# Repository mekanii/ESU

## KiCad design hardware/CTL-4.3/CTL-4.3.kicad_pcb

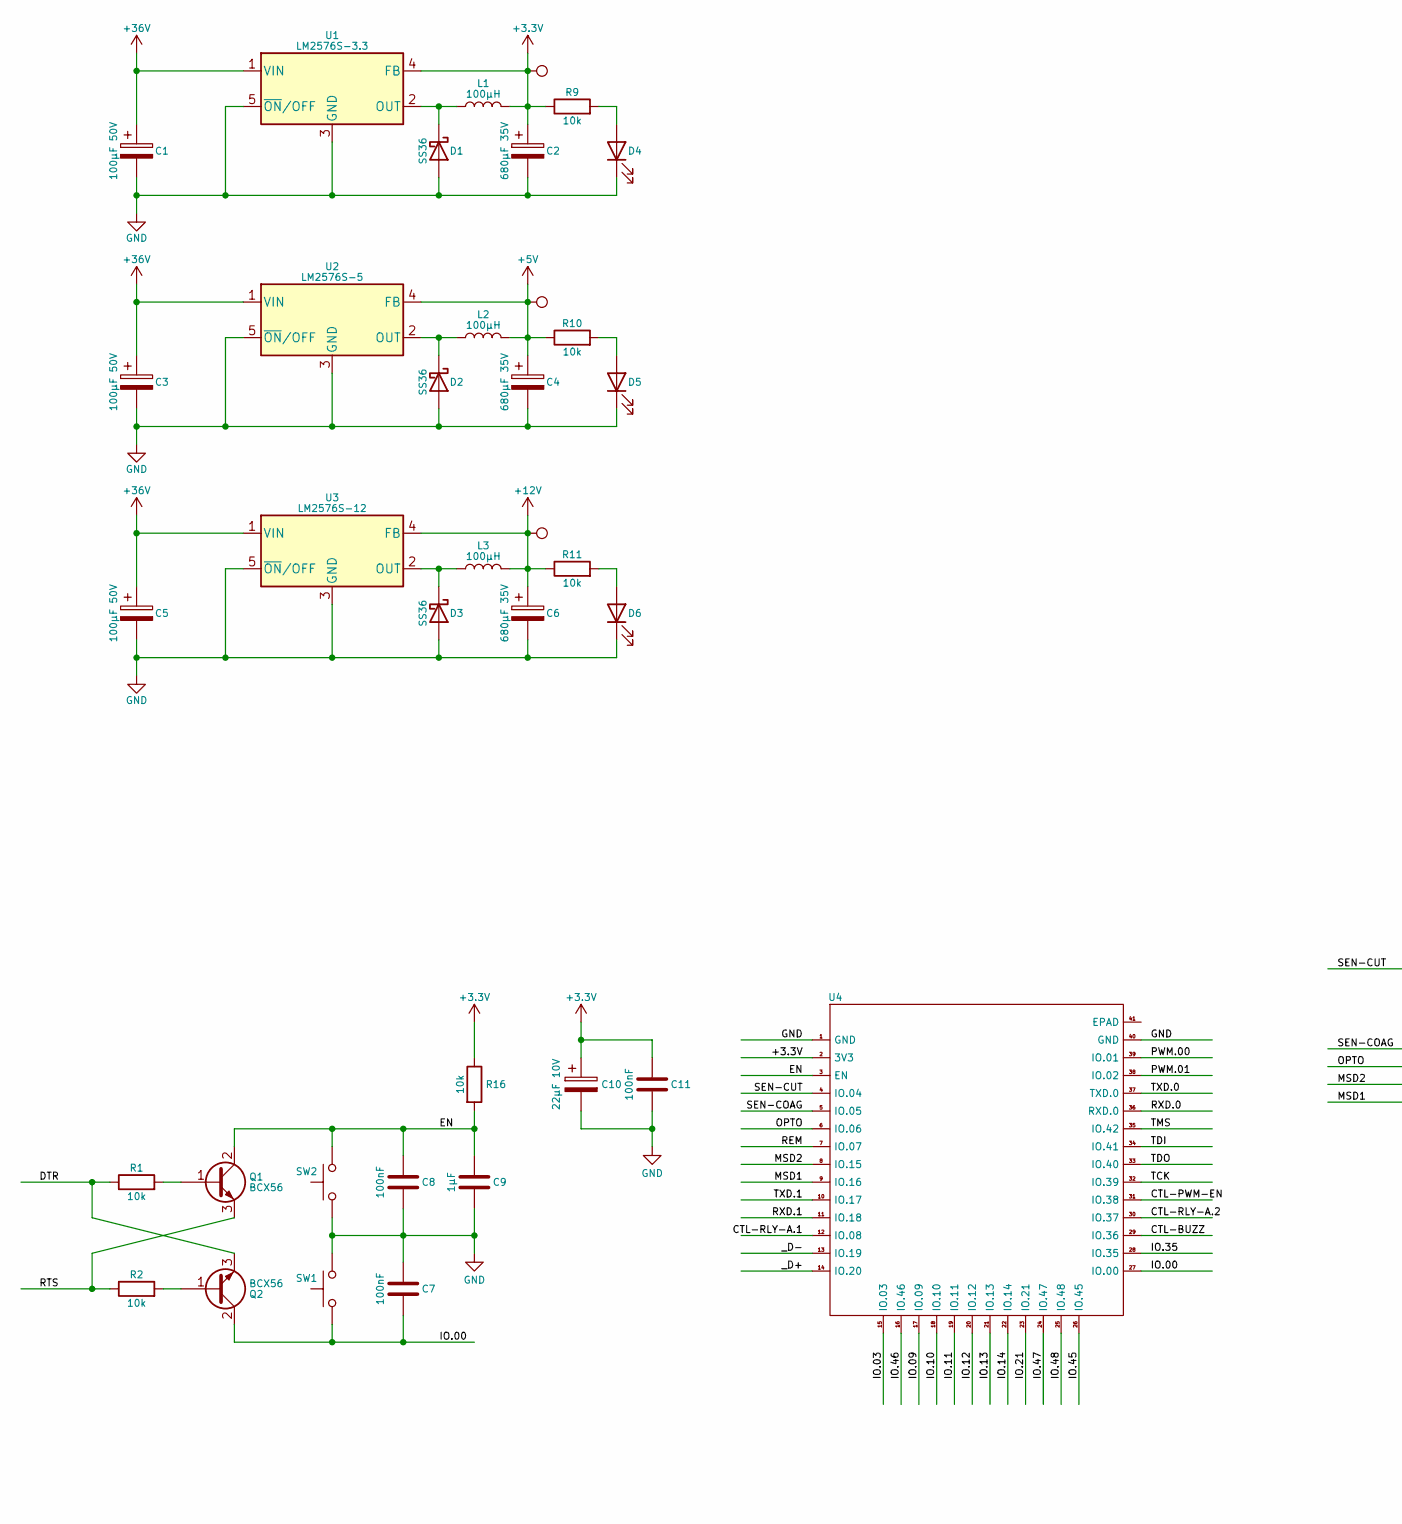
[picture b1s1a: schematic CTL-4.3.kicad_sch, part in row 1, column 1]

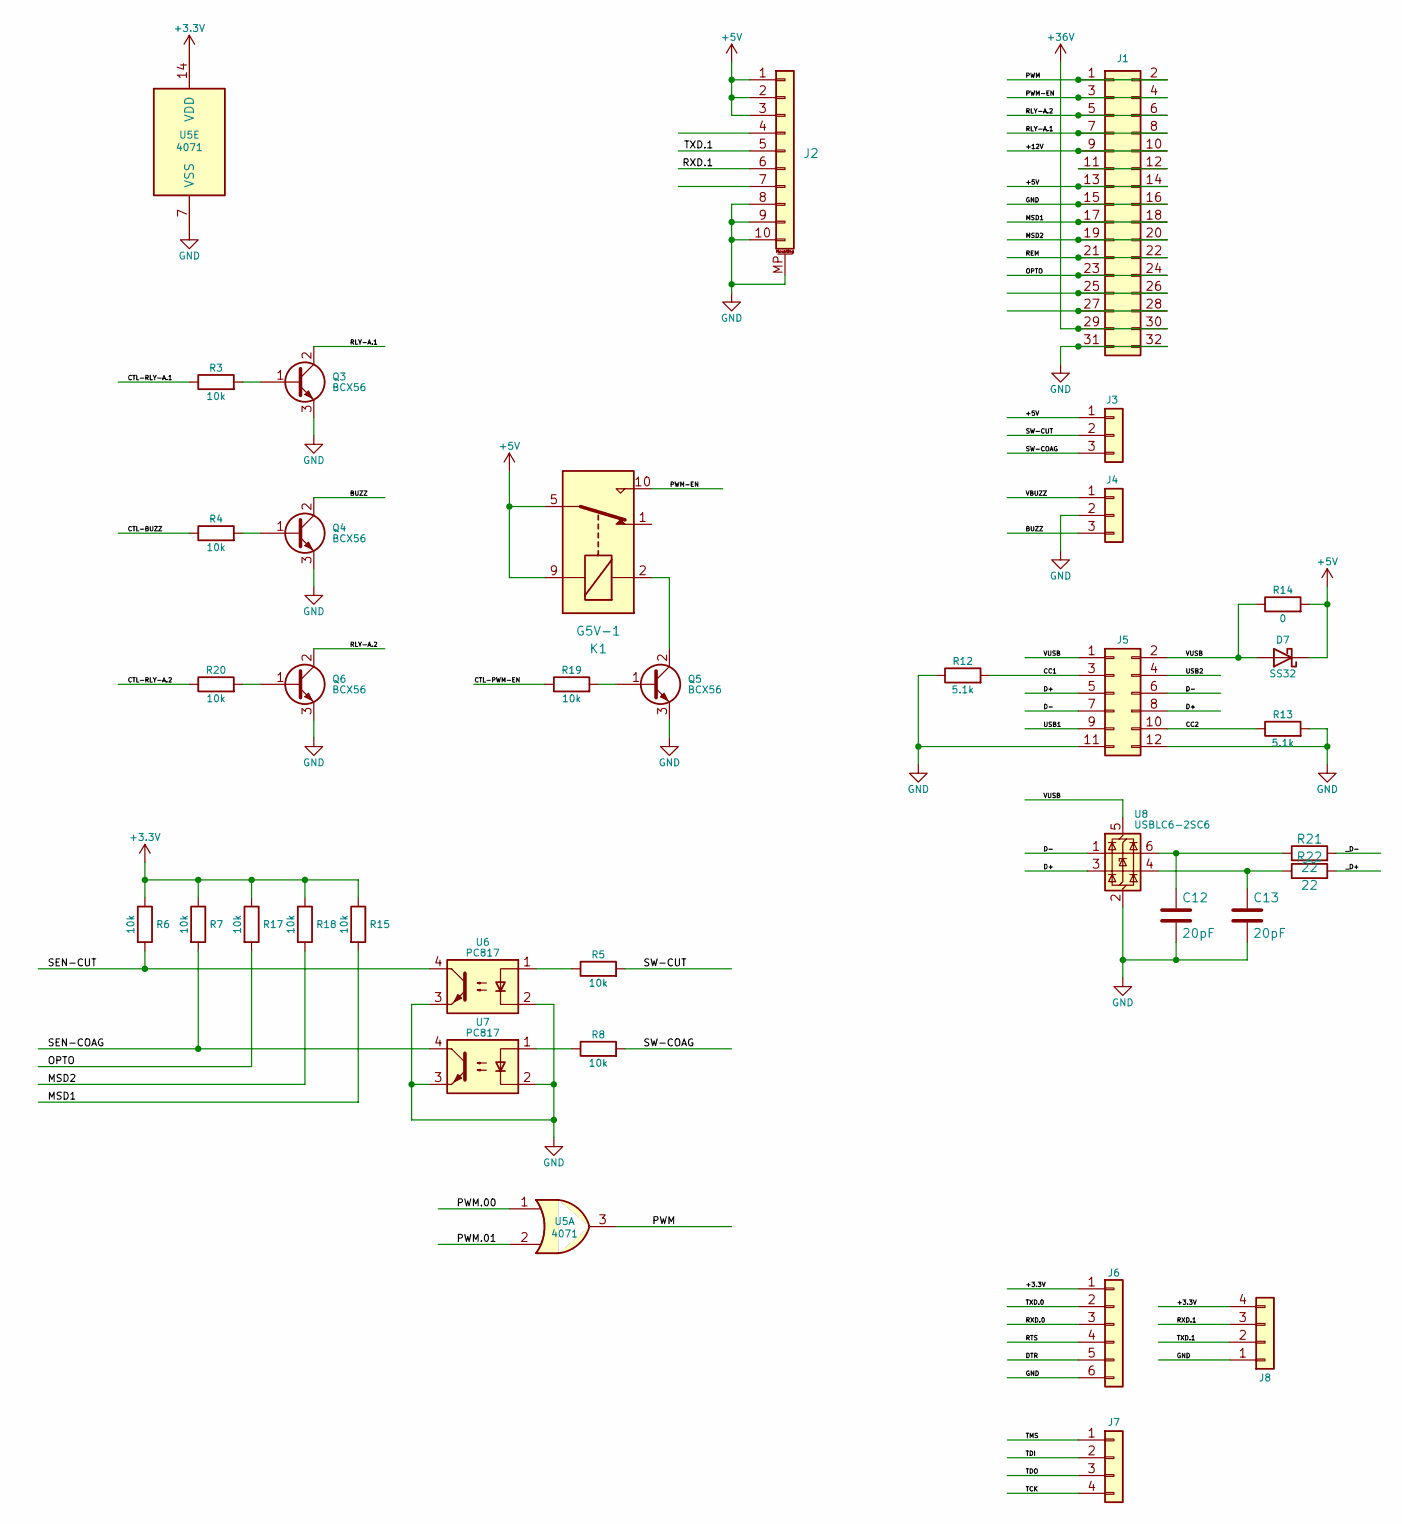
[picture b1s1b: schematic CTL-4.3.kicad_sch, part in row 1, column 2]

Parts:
C1, C3, C5: 100µF 50V; CP_Elec_10x10
C2, C4, C6: 680µF 35V; CP_Elec_10x10
C7, C8, C11: 100nF; C_0805_2012Metric_Pad1.18x1.45mm_HandSolder
C9: 1µF; C_0805_2012Metric_Pad1.18x1.45mm_HandSolder
C10: 22µF 10V; CP_EIA-3216-18_Kemet-A_Pad1.58x1.35mm_HandSolder
C12, C13: 20pF; C_0805_2012Metric_Pad1.18x1.45mm_HandSolder
D1, D2, D3: SS36; D_SMA
D4, D5, D6: LED; LED_0805_2012Metric_Pad1.15x1.40mm_HandSolder
D7: SS32; D_SMA
J1: Conn_02x16_Top_Bottom; PinHeader_2x16_P2.54mm_Horizontal_NoPins
J2: TE_1-84952-0_1x10-1MP_P1.0mm_Horizontal
J3, J4: Conn_01x03; JST_XH_B3B-XH-A_1x03_P2.50mm_Vertical
J5: Conn_02x06_Odd_Even; PinHeader_2x06_P2.54mm_Vertical
J6: Conn_01x04; PinHeader_1x06_P2.54mm_Vertical
J7, J8: Conn_01x04; PinHeader_1x04_P2.54mm_Vertical
K1: G5V-1; Relay_SPDT_Omron_G5V-1
L1, L2, L3: 100µH; L_12x12mm_H8mm
Q1, Q2, Q3, Q4, Q5, Q6: BCX56; SOT-89-3
R1, R2, R3, R4, R5, R6, R7, R8, R9, R10, R11, R15, R16, R17, R18, R19, R20: 10k; R_0805_2012Metric_Pad1.20x1.40mm_HandSolder
R12, R13: 5.1k; R_0805_2012Metric_Pad1.20x1.40mm_HandSolder
R14: 0; R_1206_3216Metric_Pad1.30x1.75mm_HandSolder
R21, R22: 22; R_0805_2012Metric_Pad1.20x1.40mm_HandSolder
SW1, SW2: SW_Omron_B3FS; SW_SPST_Omron_B3FS-100xP
TP1, TP2, TP3: TestPoint; TestPoint_Bridge_Pitch2.54mm_Drill1.0mm
U1: LM2576S-3.3; TO-263-5_TabPin3
U2: LM2576S-5; TO-263-5_TabPin3
U3: LM2576S-12; TO-263-5_TabPin3
U4: ESP32-S3-WROOM-1U
U5: 4071; DIP-14_W8.89mm_SMDSocket_LongPads
U6, U7: PC817; DIP-4_W7.62mm_Socket
U8: USBLC6-2SC6; SOT-23-6

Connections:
+3.3V: C2.1, C10.1, C11.2, J6.1, J8.4, L1.2, R6.1, R7.1, R9.1, R15.1, R16.1, R17.1, R18.1, TP1.1, U1.4 (FB), U4.2 (3V3), U5.14 (VDD)
+5V: C4.1, D7.1 (K), J1.13, J1.14, J2.1, J2.2, J2.3, J3.1, K1.5, K1.6, K1.9, L2.2, R10.1, R14.2, TP2.1, U2.4 (FB)
+12V: C6.1, J1.9, J1.10, L3.2, R11.1, TP3.1, U3.4 (FB)
+36V: C1.1, C3.1, C5.1, J1.29, J1.30, U1.1 (VIN), U2.1 (VIN), U3.1 (VIN)
/BUZZ: J4.3, Q4.2 (C)
/CC1: J5.3, R12.2
/CC2: J5.10, R13.1
/CTL-BUZZ: R4.1, U4.29 (IO.36)
/CTL-PWM-EN: R19.1, U4.31 (IO.38)
/CTL-RLY-A.1: R3.1, U4.12 (IO.08)
/CTL-RLY-A.2: R20.1, U4.30 (IO.37)
/D+: J5.5, J5.8, U8.3 (I/O2)
/D-: J5.6, J5.7, U8.1 (I/O1)
/DTR: J6.5, Q2.3 (E), R1.1
/EN: C8.2, C9.2, Q1.2 (C), R16.2, SW2.2, U4.3 (EN)
/IO.00: C7.2, Q2.2 (C), SW1.1, U4.27 (IO.00)
/IO.03: U4.15 (IO.03)
/IO.09: U4.17 (IO.09)
/IO.10: U4.18 (IO.10)
/IO.11: U4.19 (IO.11)
/IO.12: U4.20 (IO.12)
/IO.13: U4.21 (IO.13)
/IO.14: U4.22 (IO.14)
/IO.21: U4.23 (IO.21)
/IO.35: U4.28 (IO.35)
/IO.45: U4.26 (IO.45)
/IO.46: U4.16 (IO.46)
/IO.47: U4.24 (IO.47)
/IO.48: U4.25 (IO.48)
/MSD1: J1.17, J1.18, R15.2, U4.9 (IO.16)
/MSD2: J1.19, J1.20, R18.2, U4.8 (IO.15)
/OPTO: J1.23, J1.24, R17.2, U4.6 (IO.06)
/PWM: J1.1, J1.2, U5.3
/PWM-EN: J1.3, J1.4, K1.10
/PWM.00: U4.39 (IO.01), U5.1
/PWM.01: U4.38 (IO.02), U5.2
/REM: J1.21, J1.22, U4.7 (IO.07)
/RLY-A.1: J1.7, J1.8, Q3.2 (C)
/RLY-A.2: J1.5, J1.6, Q6.2 (C)
/RTS: J6.4, Q1.3 (E), R2.1
/RXD.0: J6.3, U4.36 (RXD.0)
/RXD.1: J2.6, J8.3, U4.11 (IO.18)
/SEN-COAG: R7.2, U4.5 (IO.05), U7.4
/SEN-CUT: R6.2, U4.4 (IO.04), U6.4
/SW-COAG: J3.3, R8.2
/SW-CUT: J3.2, R5.2
/TCK: J7.4, U4.32 (IO.39)
/TDI: J7.2, U4.34 (IO.41)
/TDO: J7.3, U4.33 (IO.40)
/TMS: J7.1, U4.35 (IO.42)
/TXD.0: J6.2, U4.37 (TXD.0)
/TXD.1: J2.5, J8.2, U4.10 (IO.17)
/USB1: J5.9
/USB2: J5.4
/VBUZZ: J4.1
/VUSB: D7.2 (A), J5.1, J5.2, R14.1, U8.5 (VBUS)
/_D+: R22.2, U4.14 (IO.20)
/_D-: R21.2, U4.13 (IO.19)
GND: C1.2, C2.2, C3.2, C4.2, C5.2, C6.2, C7.1, C8.1, C9.1, C10.2, C11.1, C12.2, C13.2, D1.2 (A), D2.2 (A), D3.2 (A), D4.1 (K), D5.1 (K), D6.1 (K), J1.15, J1.16, J1.31, J1.32, J2.8, J2.9, J2.10, J2.MP (MountPin), J4.2, J5.11, J5.12, J6.6, J8.1, Q3.3 (E), Q4.3 (E), Q5.3 (E), Q6.3 (E), R12.1, R13.2, SW1.2, SW2.1, U1.3 (GND), U1.5 (~ON/OFF), U2.3 (GND), U2.5 (~ON/OFF), U3.3 (GND), U3.5 (~ON/OFF), U4.1 (GND), U4.40 (GND), U5.7 (VSS), U6.2, U6.3, U7.2, U7.3, U8.2 (GND)
unnamed: C12.1, R21.1, U8.6 (I/O1)
unnamed: C13.1, R22.1, U8.4 (I/O2)
unnamed: D1.1 (K), L1.1, U1.2 (OUT)
unnamed: D2.1 (K), L2.1, U2.2 (OUT)
unnamed: D3.1 (K), L3.1, U3.2 (OUT)
unnamed: D4.2 (A), R9.2
unnamed: D5.2 (A), R10.2
unnamed: D6.2 (A), R11.2
unnamed: J1.11, J1.12
unnamed: J1.25, J1.26
unnamed: J1.27, J1.28
unnamed: Q1.1 (B), R1.2
unnamed: Q2.1 (B), R2.2
unnamed: Q3.1 (B), R3.2
unnamed: Q4.1 (B), R4.2
unnamed: Q5.1 (B), R19.2
unnamed: K1.2, Q5.2 (C)
unnamed: Q6.1 (B), R20.2
unnamed: R5.1, U6.1
unnamed: R8.1, U7.1

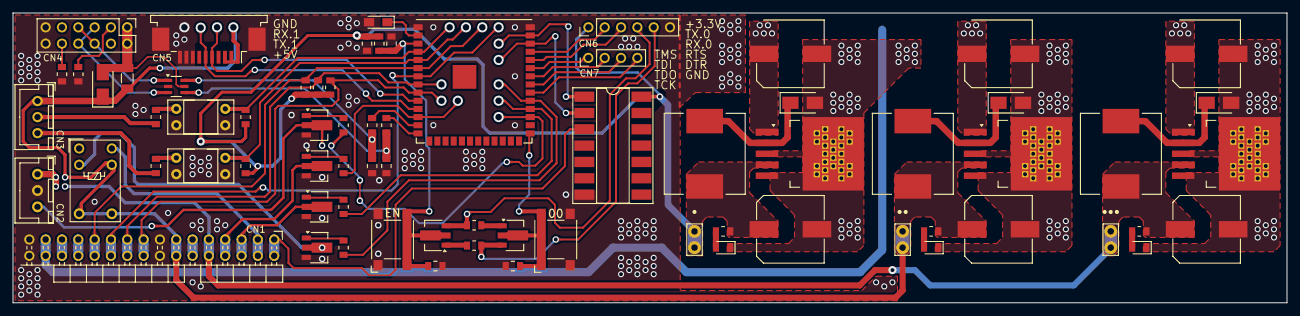
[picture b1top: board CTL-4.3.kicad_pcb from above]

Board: 2 copper layers, 198.2 x 45.1 mm, 72 parts (0 on the bottom side), 63 nets.

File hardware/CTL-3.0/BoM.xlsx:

# | Sourced | Placed | References | Value | Footprint | Quantity
1 | ✅ |  | R1, R2, R3, R4, R5, R6, R7, R8, R9, R10, R11, R15, R16, R17, R18, R19 | 10k | R_1206_3216Metric_Pad1.30x1.75mm_HandSolder | 16 | https://www.tokopedia.com/lisuinstrument/10k-1206-1-250mw-20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
2 | ✅ |  | R12, R13 | 5.1k | R_1206_3216Metric_Pad1.30x1.75mm_HandSolder | 2 | https://www.tokopedia.com/lisuinstrument/5-1k-1206-1-250mw-2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
3 | ✅ |  | R14 | 0 | R_1206_3216Metric_Pad1.30x1.75mm_HandSolder | 1 | https://www.tokopedia.com/lisuinstrument/0-1206-5-smd-thick-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
4 | ✅ |  | C1, C3, C5 | 100µF 35V | CP_Elec_10x10 | 3 | https://www.tokopedia.com/jayenk/solid-kapasitor-capasitor-e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
5 | ✅ |  | C2, C4, C6 | 680µF 35V | CP_Elec_10x10 | 3 | https://www.tokopedia.com/jayenk/solid-kapasitor-capasitor-e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
6 | ✅ |  | C7, C8, C11 | 100nF | C_1206_3216Metric_Pad1.33x1.80mm_HandSolder | 3 | https://www.tokopedia.com/lisuinstrument/100nf-50v-x7r-10-12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
7 | ✅ |  | C9 | 1µF | C_1206_3216Metric_Pad1.33x1.80mm_HandSolder | 1 | https://www.tokopedia.com/lisuinstrument/1uf-10-50v-x7r-1206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
8 | ✅ |  | C10 | 22µF 10V | CP_EIA-3528-12_Kemet-T_Pad1.50x2.35mm_HandSolder | 1 | https://www.tokopedia.com/putraniagabdg/tantalum-smd-22uf-10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
9 | ✅ |  | L1, L2, L3 | 100µH | L_12x12mm_H8mm | 3 | https://www.tokopedia.com/elantech/induktor-smd-100uh-1-7a-1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
10 | ✅ |  | D1, D2, D3 | SS36 | D_SMA | 3 | https://www.tokopedia.com/lisuinstrument/ss36a-60v-3a-schott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
11 | ✅ |  | D4, D5, D6 | LED | LED_1206_3216Metric_Pad1.42x1.75mm_HandSolder | 3 | https://www.tokopedia.com/lisuinstrument/1206-smd-led-smt-ul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
12 | ✅ |  | D7 | BAT60A | D_SMB_Handsoldering | 1 | https://www.tokopedia.com/lisuinstrument/ss36b-60v-3a-schott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
13 | ✅ |  | U6, U7 | PC817 | DIP-4_W7.62mm_Socket | 2 | https://www.tokopedia.com/putraniagabdg/pc817-optocoupler-pc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
14 | ✅ |  | U1 | LM2576S-3.3 | TO-263-5_TabPin3 | 1 | https://www.tokopedia.com/starelektro-1/lm2576s-lm2576hvs-ad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
15 | ✅ |  | U2 | LM2576S-5 | TO-263-5_TabPin3 | 1 | https://www.tokopedia.com/starelektro-1/lm2576s-lm2576hvs-ad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
16 | ✅ |  | U3 | LM2576S-12 | TO-263-5_TabPin3 | 1 | https://www.tokopedia.com/starelektro-1/lm2576s-lm2576hvs-ad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
17 | ✅ |  | U4 | ESP32-S3-WROOM-1U | ESP32-S3-WROOM-1U | 1 | https://www.tokopedia.com/the-diy-store/esp32-s3-wroom-esp32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
18 | ✅ |  | U5 | 4071 | DIP-14_W8.89mm_SMDSocket_LongPads | 1 | https://www.tokopedia.com/smgjayatronik/cd4071bcm-cd4071-smd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
19 | ✅ |  | SW1, SW2 | SW_Omron_B3FS | SW_SPST_Omron_B3FS-100xP | 2 | https://www.tokopedia.com/putraniagabdg/push-on-4p-mini-pcb-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
20 | ✅ |  | Q1, Q2, Q3, Q4, Q5 | BCX56 | SOT-89-3 | 5 | https://www.tokopedia.com/lisuinstrument/bcx56-npn-80v-1a-50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
21 | ✅ |  | TP1, TP2, TP3 | TestPoint | TestPoint_Bridge_Pitch2.54mm_Drill1.0mm | 3
22 | ✅ |  | K1 | G5V-1 | Relay_SPDT_Omron_G5V-1 | 1 | https://www.tokopedia.com/celectro/relay-g5v-1-5vdc
23 | ✅ |  | J7, J8 | Conn_01x04 | PinHeader_1x04_P2.54mm_Vertical | 2
24 | ✅ |  | J1 | Conn_02x16_Top_Bottom | PinHeader_2x16_P2.54mm_Horizontal_NoPins | 1 | https://www.tokopedia.com/putraniagabdg/header-male-siku-2x4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
25 | ✅ |  | J3 | Conn_01x03 | Molex_KK-396_5273-03A_1x03_P3.96mm_Vertical | 1 | https://www.tokopedia.com/putraniagabdg/1-set-konektor-heade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
26 | ✅ |  | J4 | Conn_01x02 | Molex_KK-396_5273-02A_1x02_P3.96mm_Vertical | 1 | https://www.tokopedia.com/putraniagabdg/1-set-konektor-heade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
27 | ✅ |  | J5 | Conn_02x06_Odd_Even | PinHeader_2x06_P2.54mm_Vertical | 1 | https://www.tokopedia.com/putraniagabdg/header-male-baris-2x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
28 | ✅ |  | J6 | Conn_01x04 | PinHeader_1x06_P2.54mm_Vertical | 1 | https://www.tokopedia.com/putraniagabdg/header-male-baris-1x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

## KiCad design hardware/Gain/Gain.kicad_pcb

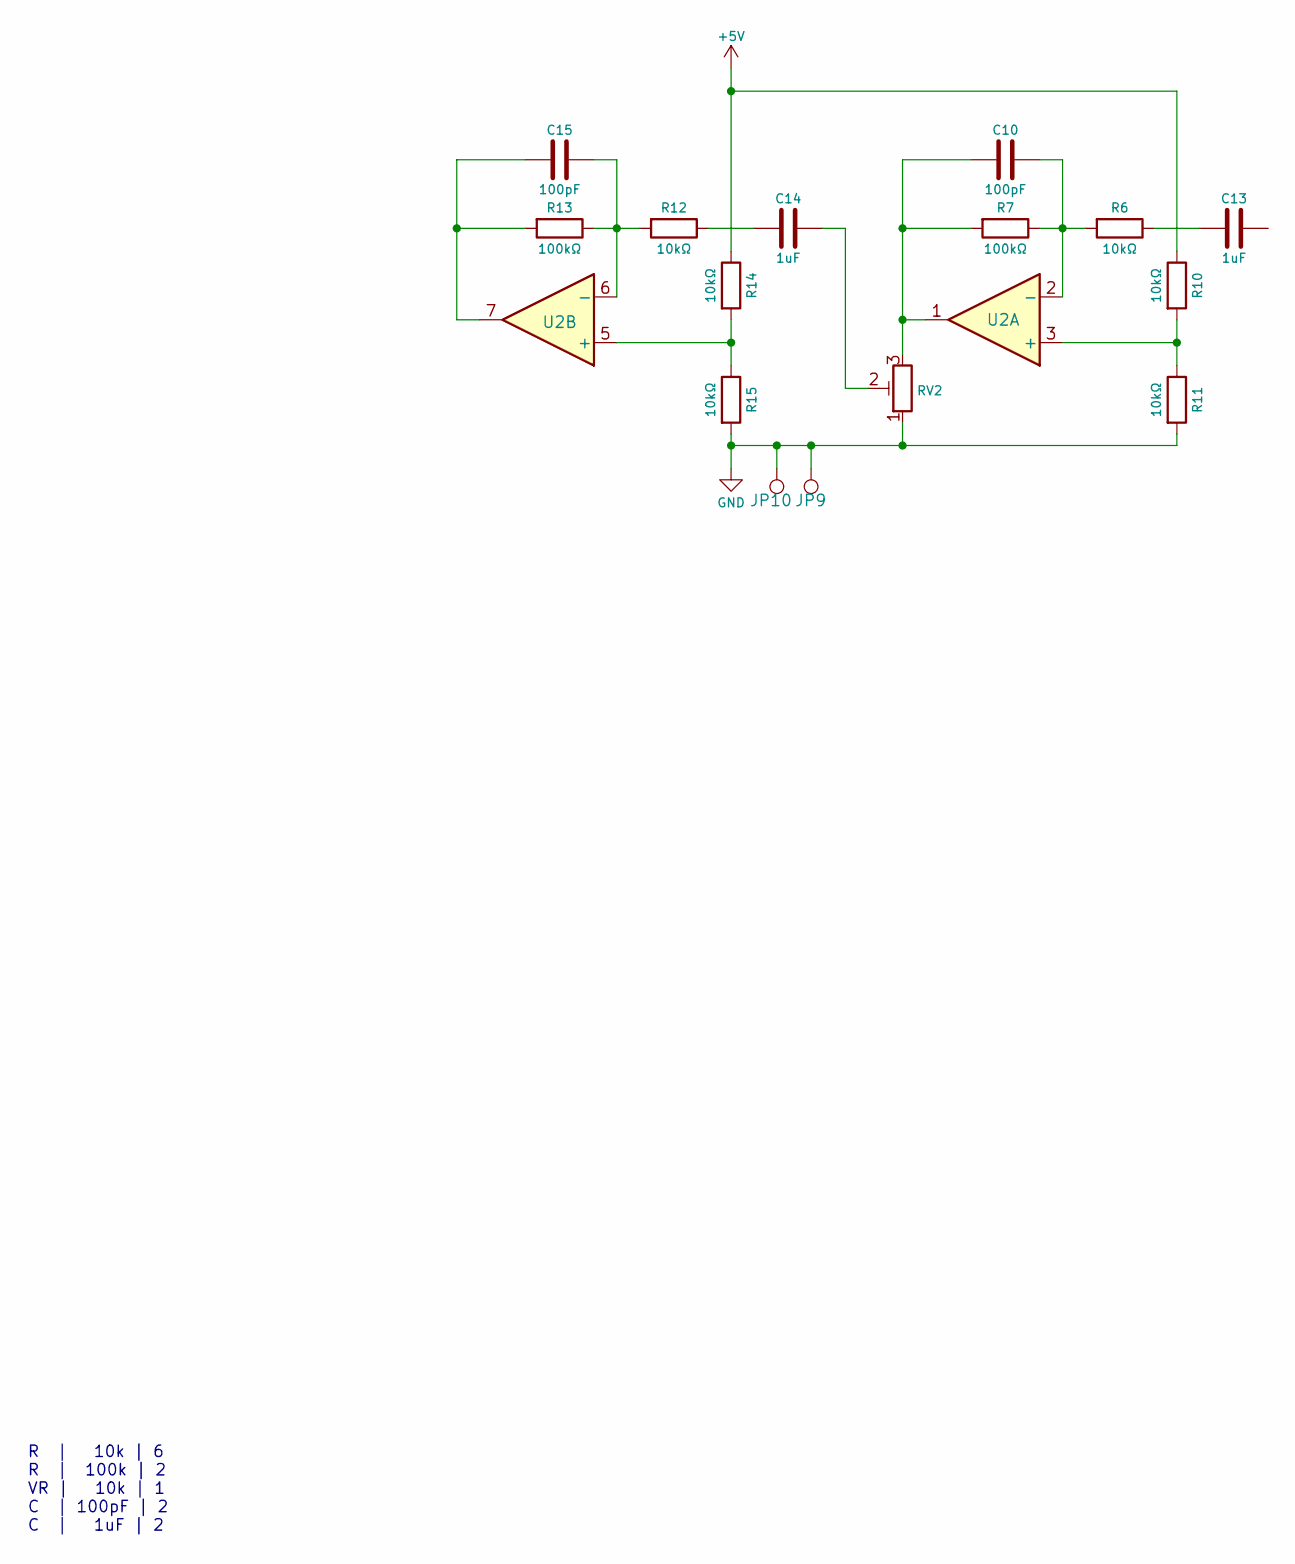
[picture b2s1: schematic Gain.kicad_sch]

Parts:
C10, C15: 100pF; C_Rect_L7.2mm_W4.5mm_P5.00mm_FKS2_FKP2_MKS2_MKP2
C13, C14: 1uF; C_Rect_L7.2mm_W4.5mm_P5.00mm_FKS2_FKP2_MKS2_MKP2
JP9, JP10: TestPoint; TestPoint_THTPad_D1.5mm_Drill0.7mm
R6, R10, R11, R12, R14, R15: 10kΩ; R_Axial_DIN0204_L3.6mm_D1.6mm_P7.62mm_Horizontal
R7, R13: 100kΩ; R_Axial_DIN0204_L3.6mm_D1.6mm_P7.62mm_Horizontal
RV2: 1kΩ; Potentiometer_Bourns_3296X_Horizontal
U2: LM358; DIP-8_W7.62mm_Socket

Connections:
+5V: R10.1, R14.1
GND: JP9.1, JP10.1, R11.2, R15.2, RV2.1
unnamed: C10.1, R7.2, RV2.3, U2.1
unnamed: C13.1, R6.1
unnamed: C14.1, R12.1
unnamed: C14.2, RV2.2
unnamed: C15.1, R13.2, U2.7
unnamed: R10.2, R11.1, U2.3 (+)
unnamed: C10.2, R6.2, R7.1, U2.2 (-)
unnamed: R14.2, R15.1, U2.5 (+)
unnamed: C15.2, R12.2, R13.1, U2.6 (-)

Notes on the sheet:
R | 10k | 6 R | 100k | 2 VR | 10k | 1 C | 100pF | 2 C | 1uF | 2

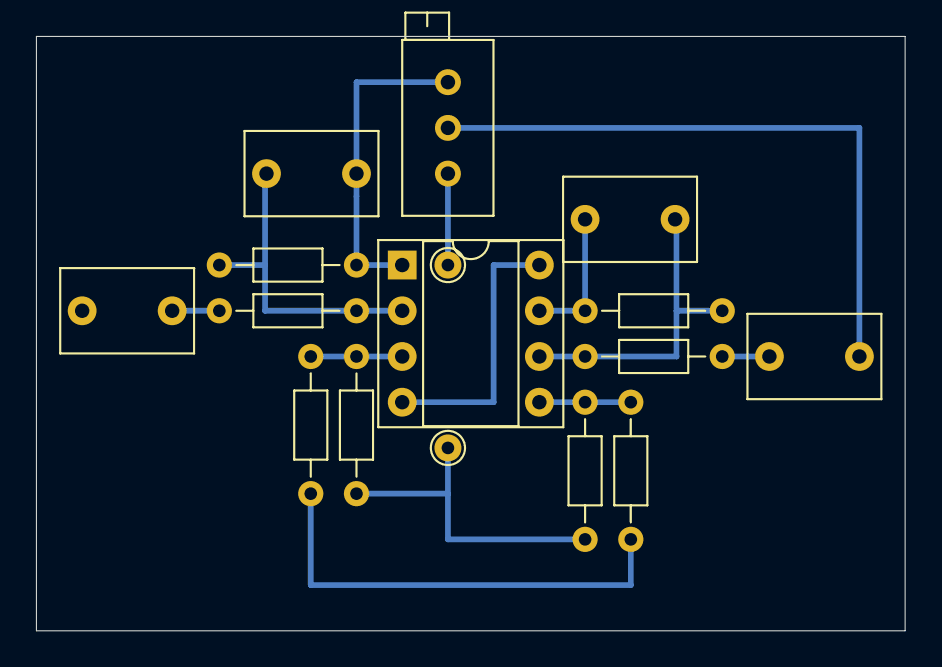
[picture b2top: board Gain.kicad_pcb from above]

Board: 2 copper layers, 48.3 x 33.0 mm, 16 parts (0 on the bottom side), 11 nets.

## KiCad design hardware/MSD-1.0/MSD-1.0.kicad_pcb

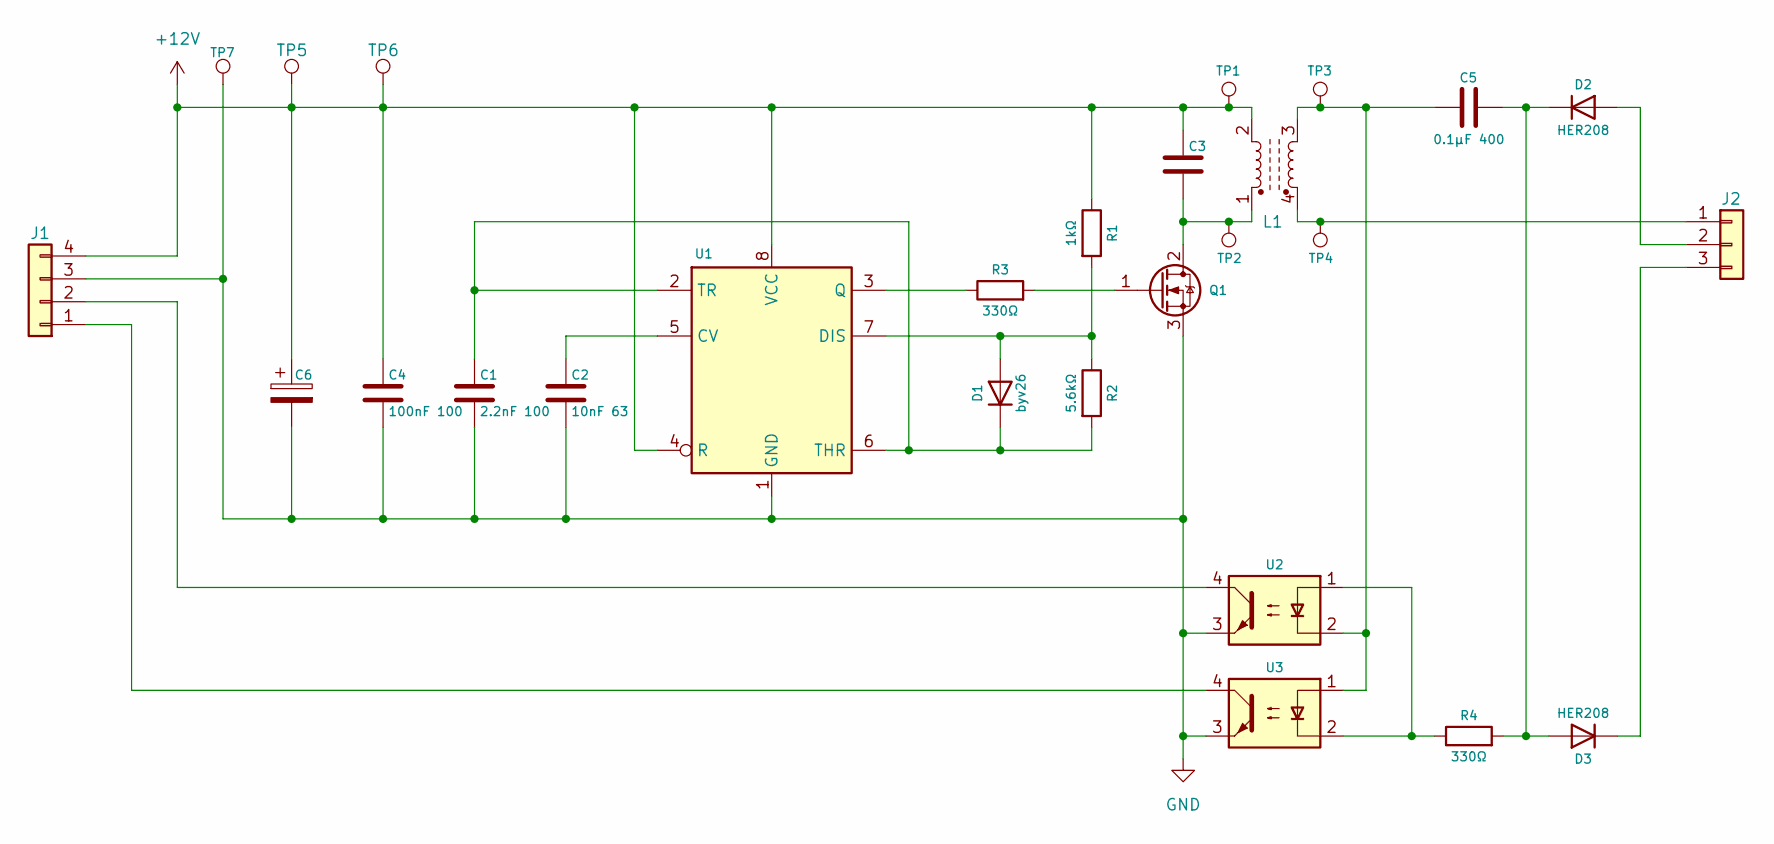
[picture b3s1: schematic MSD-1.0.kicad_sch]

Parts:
C1: 2.2nF 100; C_Rect_L7.0mm_W3.5mm_P5.00mm
C2: 10nF 63; C_Rect_L7.0mm_W3.5mm_P5.00mm
C3: 0.022µF 400; C_Rect_L13.0mm_W5.0mm_P10.00mm_FKS3_FKP3_MKS4
C4: 100nF 100; C_Rect_L7.0mm_W3.5mm_P5.00mm
C5: 0.1µF 400; C_Rect_L19.0mm_W7.0mm_P15.00mm_MKS4
C6: 470µF 35V; CP_Radial_D12.5mm_P5.00mm
D1: byv26; D_DO-35_SOD27_P7.62mm_Horizontal
D2, D3: HER208; D_DO-34_SOD68_P7.62mm_Horizontal
J1: Conn_01x05; PinHeader_1x04_P2.54mm_Horizontal_2
J2: Conn_01x03; PinHeader_1x03_P5.08mm_Horizontal_2
L1: L_Ferrite_Coupled; L_CommonMode_Toroid_Horizontal_OD23mm_ID14mm_H8mm
Q1: IRF840; TO-220-3_Horizontal_TabDown
R1: 1kΩ; R_Axial_DIN0204_L3.6mm_D1.6mm_P7.62mm_Horizontal
R2: 5.6kΩ; R_Axial_DIN0204_L3.6mm_D1.6mm_P7.62mm_Horizontal
R3, R4: 330Ω; R_Axial_DIN0204_L3.6mm_D1.6mm_P7.62mm_Horizontal
TP1, TP2, TP3, TP4, TP7: TestPoint; TestPoint_Bridge_Pitch2.54mm_Drill1.0mm
TP5, TP6: TestPoint; TestPoint_THTPad_2.0x2.0mm_Drill1.0mm_NoSilkscreen
U1: NE555P; DIP-8_W7.62mm_Socket
U2, U3: PC817; DIP-4_W7.62mm_Socket

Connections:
+12V: C3.1, C4.1, C6.1, J1.4, L1.2, R1.1, TP1.1, TP5.1, TP6.1, U1.4 (R), U1.8 (VCC)
GND: C1.2, C2.2, C4.2, C6.2, J1.3, Q1.3 (S), TP7.1, U1.1 (GND), U2.3, U3.3
unnamed: C5.1, L1.3, TP3.1, U2.2, U3.1
unnamed: D1.2 (A), R1.2, R2.1, U1.7 (DIS)
unnamed: C1.1, D1.1 (K), R2.2, U1.2 (TR), U1.6 (THR)
unnamed: D2.2 (A), J2.2
unnamed: C5.2, D2.1 (K), D3.2 (A), R4.2
unnamed: D3.1 (K), J2.3
unnamed: J1.1, U3.4
unnamed: J1.2, U2.4
unnamed: J2.1, L1.4, TP4.1
unnamed: C3.2, L1.1, Q1.2 (D), TP2.1
unnamed: Q1.1 (G), R3.2
unnamed: R4.1, U2.1, U3.2
unnamed: C2.1, U1.5 (CV)
unnamed: R3.1, U1.3 (Q)

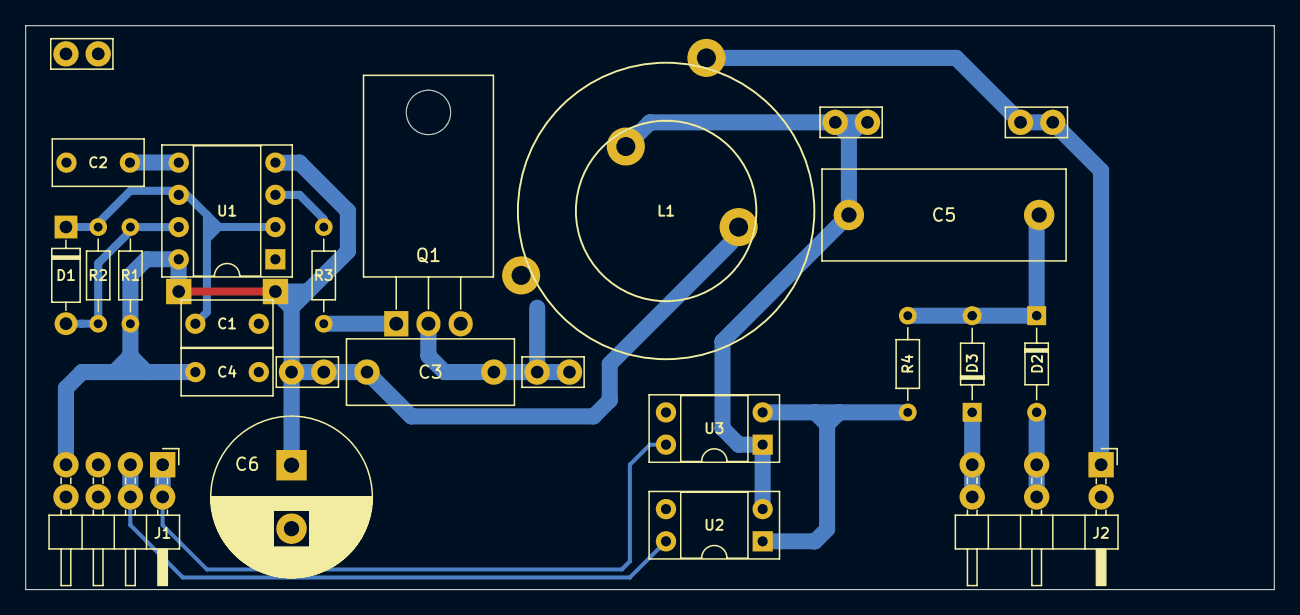
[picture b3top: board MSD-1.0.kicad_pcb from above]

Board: 2 copper layers, 98.4 x 44.4 mm, 27 parts (0 on the bottom side), 16 nets.

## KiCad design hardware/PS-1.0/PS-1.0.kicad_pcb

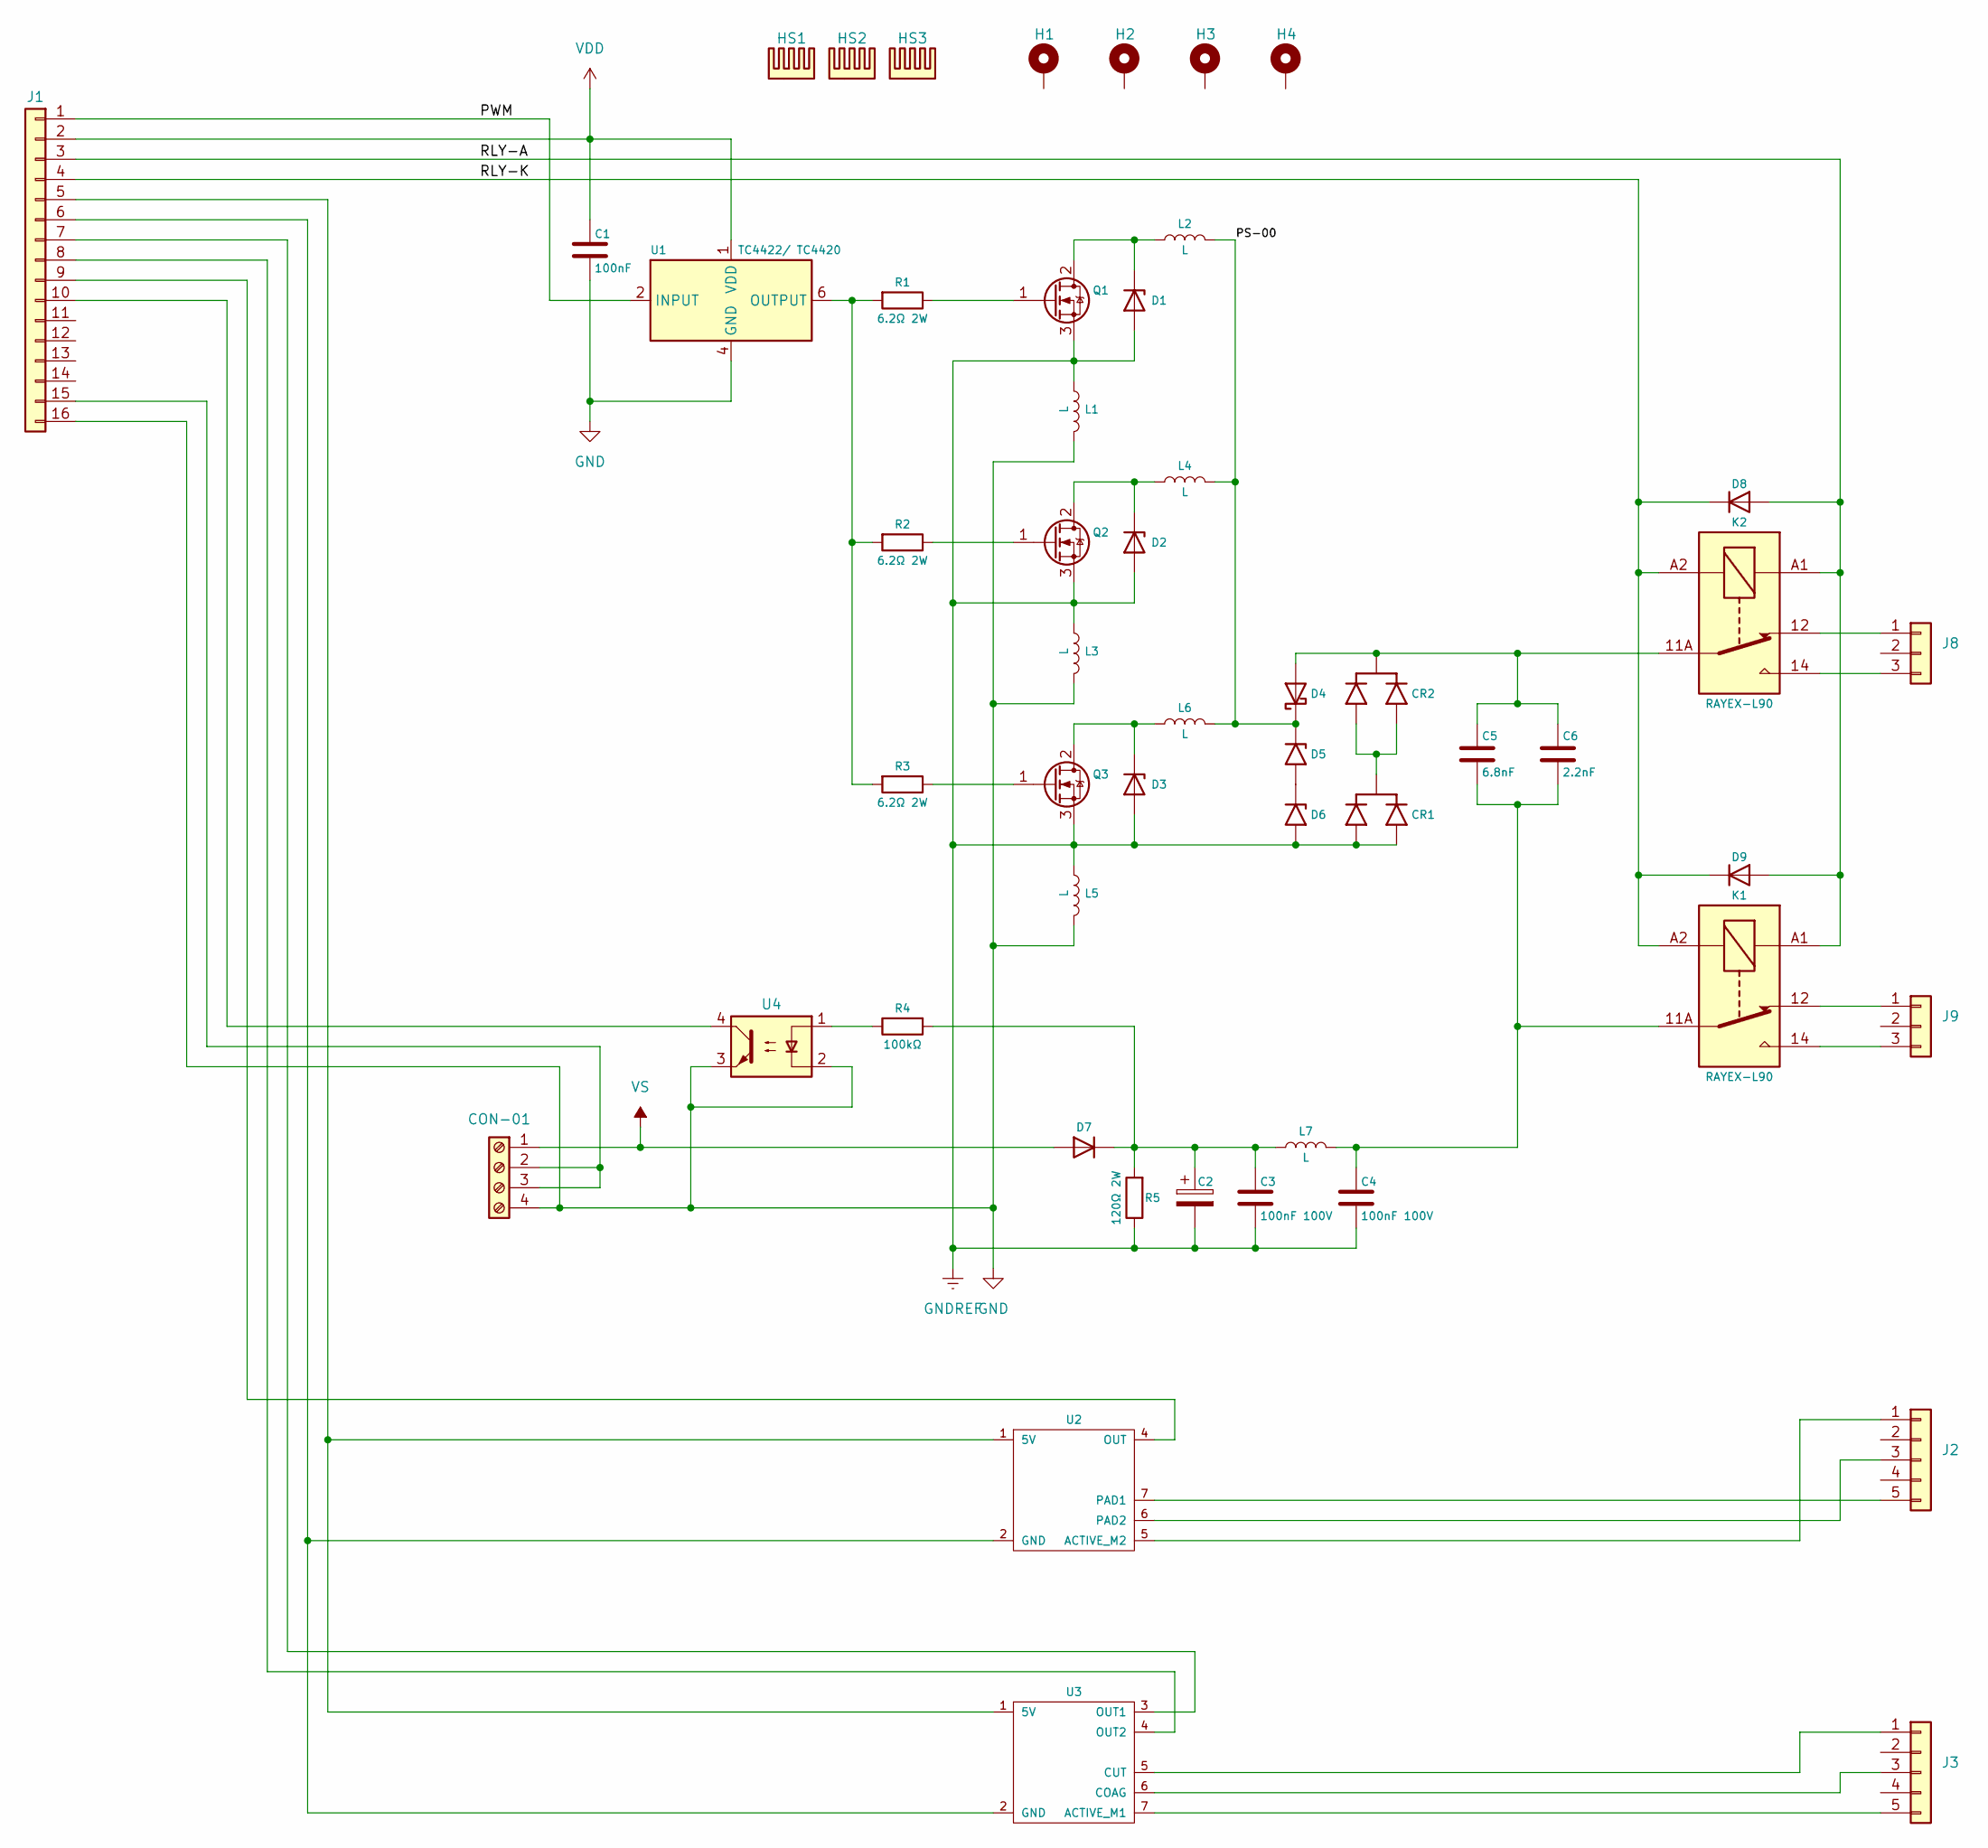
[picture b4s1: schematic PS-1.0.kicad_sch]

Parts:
C1: 100nF; C_Rect_L7.2mm_W3.5mm_P5.00mm_FKS2_FKP2_MKS2_MKP2
C2: 1000µF 160V; CP_Radial_D22.0mm_P10.00mm_SnapIn
C3, C4: 100nF 100V; C_Rect_L7.2mm_W3.5mm_P5.00mm_FKS2_FKP2_MKS2_MKP2
C5: 6.8nF; C_Rect_L13.0mm_W5.0mm_P10.00mm_FKS3_FKP3_MKS4
C6: 2.2nF; C_Rect_L13.0mm_W5.0mm_P10.00mm_FKS3_FKP3_MKS4
CON-01: KF7.62-4; KF7.62-4Pole
CR1, CR2: STTH1002CT; TO-220-3_Vertical
D1, D2, D3: 1N4746A; D_DO-41_SOD81_P10.16mm_Horizontal
D4: SB5H100/ SB5100; D_DO-201AE_P15.24mm_Horizontal
D5, D6: 1.5KE56A; D_DO-201AE_P15.24mm_Horizontal
D7: 10A10; D_DO-201AE_P15.24mm_Horizontal
D8, D9: 1N4148; D_DO-35_SOD27_P7.62mm_Horizontal
H1, H2, H3, H4: MountingHole_Pad; MountingHole_3.2mm_M3_ISO14580_Pad
HS1, HS2: Heatsink; Heatsink_Stonecold_HS-132_32x14mm_2xFixation1.5mm_NoPad
HS3: Heatsink; Heatsink_Custom_10x18x50
J1: PinSocket_02x16_P2.54mm_Vertical; PinSocket_1x16_P2.54mm_Vertical_2
J2, J3: Conn_01x05; Molex_KK-396_5273-05A_1x05_P3.96mm_Vertical_2
J8, J9: Conn_01x03; Molex_KK-396_5273-03A_1x03_P3.96mm_Vertical_2
K1, K2: RAYEX-L90; Relay_SPDT_RAYEX-L90
L1, L2, L3, L4, L5, L6, L7: L; L_Axial_L9.5mm_D4.0mm_P15.24mm_Horizontal_Fastron_SMCC
Q1, Q2, Q3: IRFPE50; TO-247-3_Vertical
R1, R2, R3: 6.2Ω 2W; R_Axial_DIN0411_L9.9mm_D3.6mm_P15.24mm_Horizontal
R4: 100kΩ; R_Axial_DIN0204_L3.6mm_D1.6mm_P7.62mm_Horizontal
R5: 120Ω 2W; R_Axial_DIN0516_L15.5mm_D5.0mm_P20.32mm_Horizontal
U1: TC4422/ TC4420; DIP-8_W7.62mm
U2: ESU-REM-4.0
U3: ESU-MSD-1.0
U4: PC817; DIP-4_W7.62mm_Socket

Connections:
/PS-00: D4.1 (K), D5.1 (A1), L2.2, L4.2, L6.2
/PWM: J1.1, U1.2 (INPUT)
/RLY-A: D8.2 (A), D9.2 (A), J1.3, K1.A1, K2.A1
/RLY-K: D8.1 (K), D9.1 (K), J1.4, K1.A2, K2.A2
GND: C1.2, CON-01.4, J1.16, L1.2, L3.2, L5.2, U1.4 (GND), U1.5 (GND), U4.2, U4.3
GNDREF: C2.2, C3.2, C4.2, CR1.1, CR1.3, D1.2 (A), D2.2 (A), D3.2 (A), D6.2 (A2), L1.1, L3.1, L5.1, Q1.3 (S), Q2.3 (S), Q3.3 (S), R5.1
unnamed: C4.1, C5.2, C6.2, K1.11A, K1.11B, L7.2
unnamed: CON-01.2, CON-01.3, J1.15
unnamed: CR1.2, CR2.1, CR2.3
unnamed: D1.1 (K), L2.1, Q1.2 (D)
unnamed: D2.1 (K), L4.1, Q2.2 (D)
unnamed: D3.1 (K), L6.1, Q3.2 (D)
unnamed: C5.1, C6.1, CR2.2, D4.2 (A), K2.11A, K2.11B
unnamed: D5.2 (A2), D6.1 (A1)
unnamed: C2.1, C3.1, D7.1 (K), L7.1, R4.2, R5.2
unnamed: J1.5, U2.1 (5V), U3.1 (5V)
unnamed: J1.6, U2.2 (GND), U3.2 (GND)
unnamed: J1.7, U3.3 (OUT1)
unnamed: J1.8, U3.4 (OUT2)
unnamed: J1.9, U2.4 (OUT)
unnamed: J1.10, U4.4
unnamed: J2.1, U2.5 (ACTIVE_M2)
unnamed: J2.3, U2.6 (PAD2)
unnamed: J2.5, U2.7 (PAD1)
unnamed: J3.1, U3.5 (CUT)
unnamed: J3.3, U3.6 (COAG)
unnamed: J3.5, U3.7 (ACTIVE_M1)
unnamed: J8.1, K2.12
unnamed: J8.3, K2.14
unnamed: J9.1, K1.12
unnamed: J9.3, K1.14
unnamed: Q1.1 (G), R1.1
unnamed: Q2.1 (G), R2.1
unnamed: Q3.1 (G), R3.1
unnamed: R1.2, R2.2, R3.2, U1.6 (OUTPUT), U1.7 (OUTPUT)
unnamed: R4.1, U4.1
VDD: C1.1, J1.2, U1.1 (VDD), U1.8 (VDD)
VS: CON-01.1, D7.2 (A)
